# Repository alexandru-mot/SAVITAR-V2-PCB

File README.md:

# Savitar V2

Line-follower robot mainboard, designed in KiCad 10.

## Board overview

- **MCU**: ATSAMD51J19A (main), ESP32-C3-MINI-1 (wireless/telemetry)
- **USB**: USB-C input with USBLC6-2 ESD protection and an FSUSB42 USB mux
- **Power**: MT2492 buck converter + TLV75733 LDO
- **Motor drive**: dual DRV8874 H-bridges with INA240 current sensing (see the "Motor" netclass in the project settings)
- **Line sensing**: QRE1113GR IR-reflectance array, muxed through 74HC4051/74HC238, driven via a TBD62083 array, connected over FFC to the main board

## Schematic hierarchy

- `SAVITAR_V2.kicad_sch` — root sheet
  - `MCU.kicad_sch` — MCU, power, USB, motor drive
  - `SENSOR_ARRAY.kicad_sch` — IR sensor array board

## Libraries

Project-local only, referenced via `${KIPRJMOD}`:
- `symbols/SAVITAR` — consolidated project symbol library
- `footprints/SAVITAR.pretty` — consolidated project footprint library
- `models/` — 3D step models

## BOM

`BOM/SAVITAR_V2_BOM.csv` is generated directly from the schematic (reference designators, values, footprints) and is the source of truth for what's actually on the board. Regenerate it after schematic changes with:

```
kicad-cli sch export bom --group-by "Value,Footprint" --output "BOM/SAVITAR_V2_BOM.csv" "SAVITAR_V2.kicad_sch"
```

An `LCSC#` + `Notes` column has been added by hand, carried over from an earlier LCSC cart export (`BOM/archive/`). Rows with a note are either genuinely ambiguous (two different LCSC SKUs existed for the same value), not yet sourced, or flagged for a spec mismatch — check the `Notes` column before ordering. **LCSC stock/pricing changes constantly — treat this column as something to refresh right before placing an order, not something to keep current during layout.**

## Backups

`SAVITAR_V2-backups/` is local-only (gitignored) — timestamped project backups, not versioned since git already provides history.

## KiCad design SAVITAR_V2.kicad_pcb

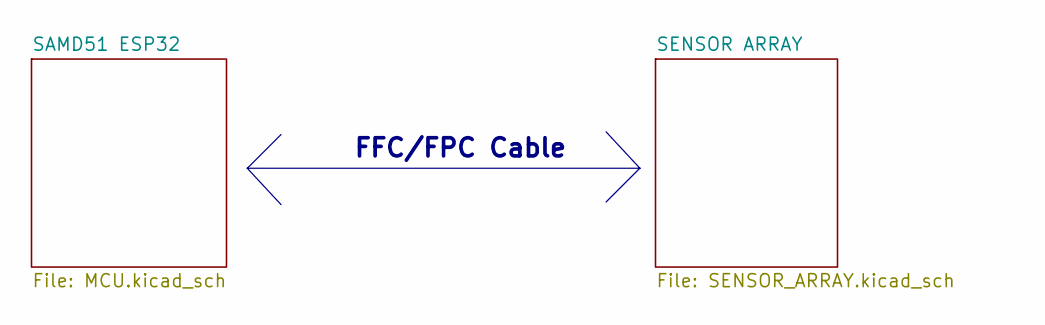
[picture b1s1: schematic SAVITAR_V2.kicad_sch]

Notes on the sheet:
FFC/FPC Cable

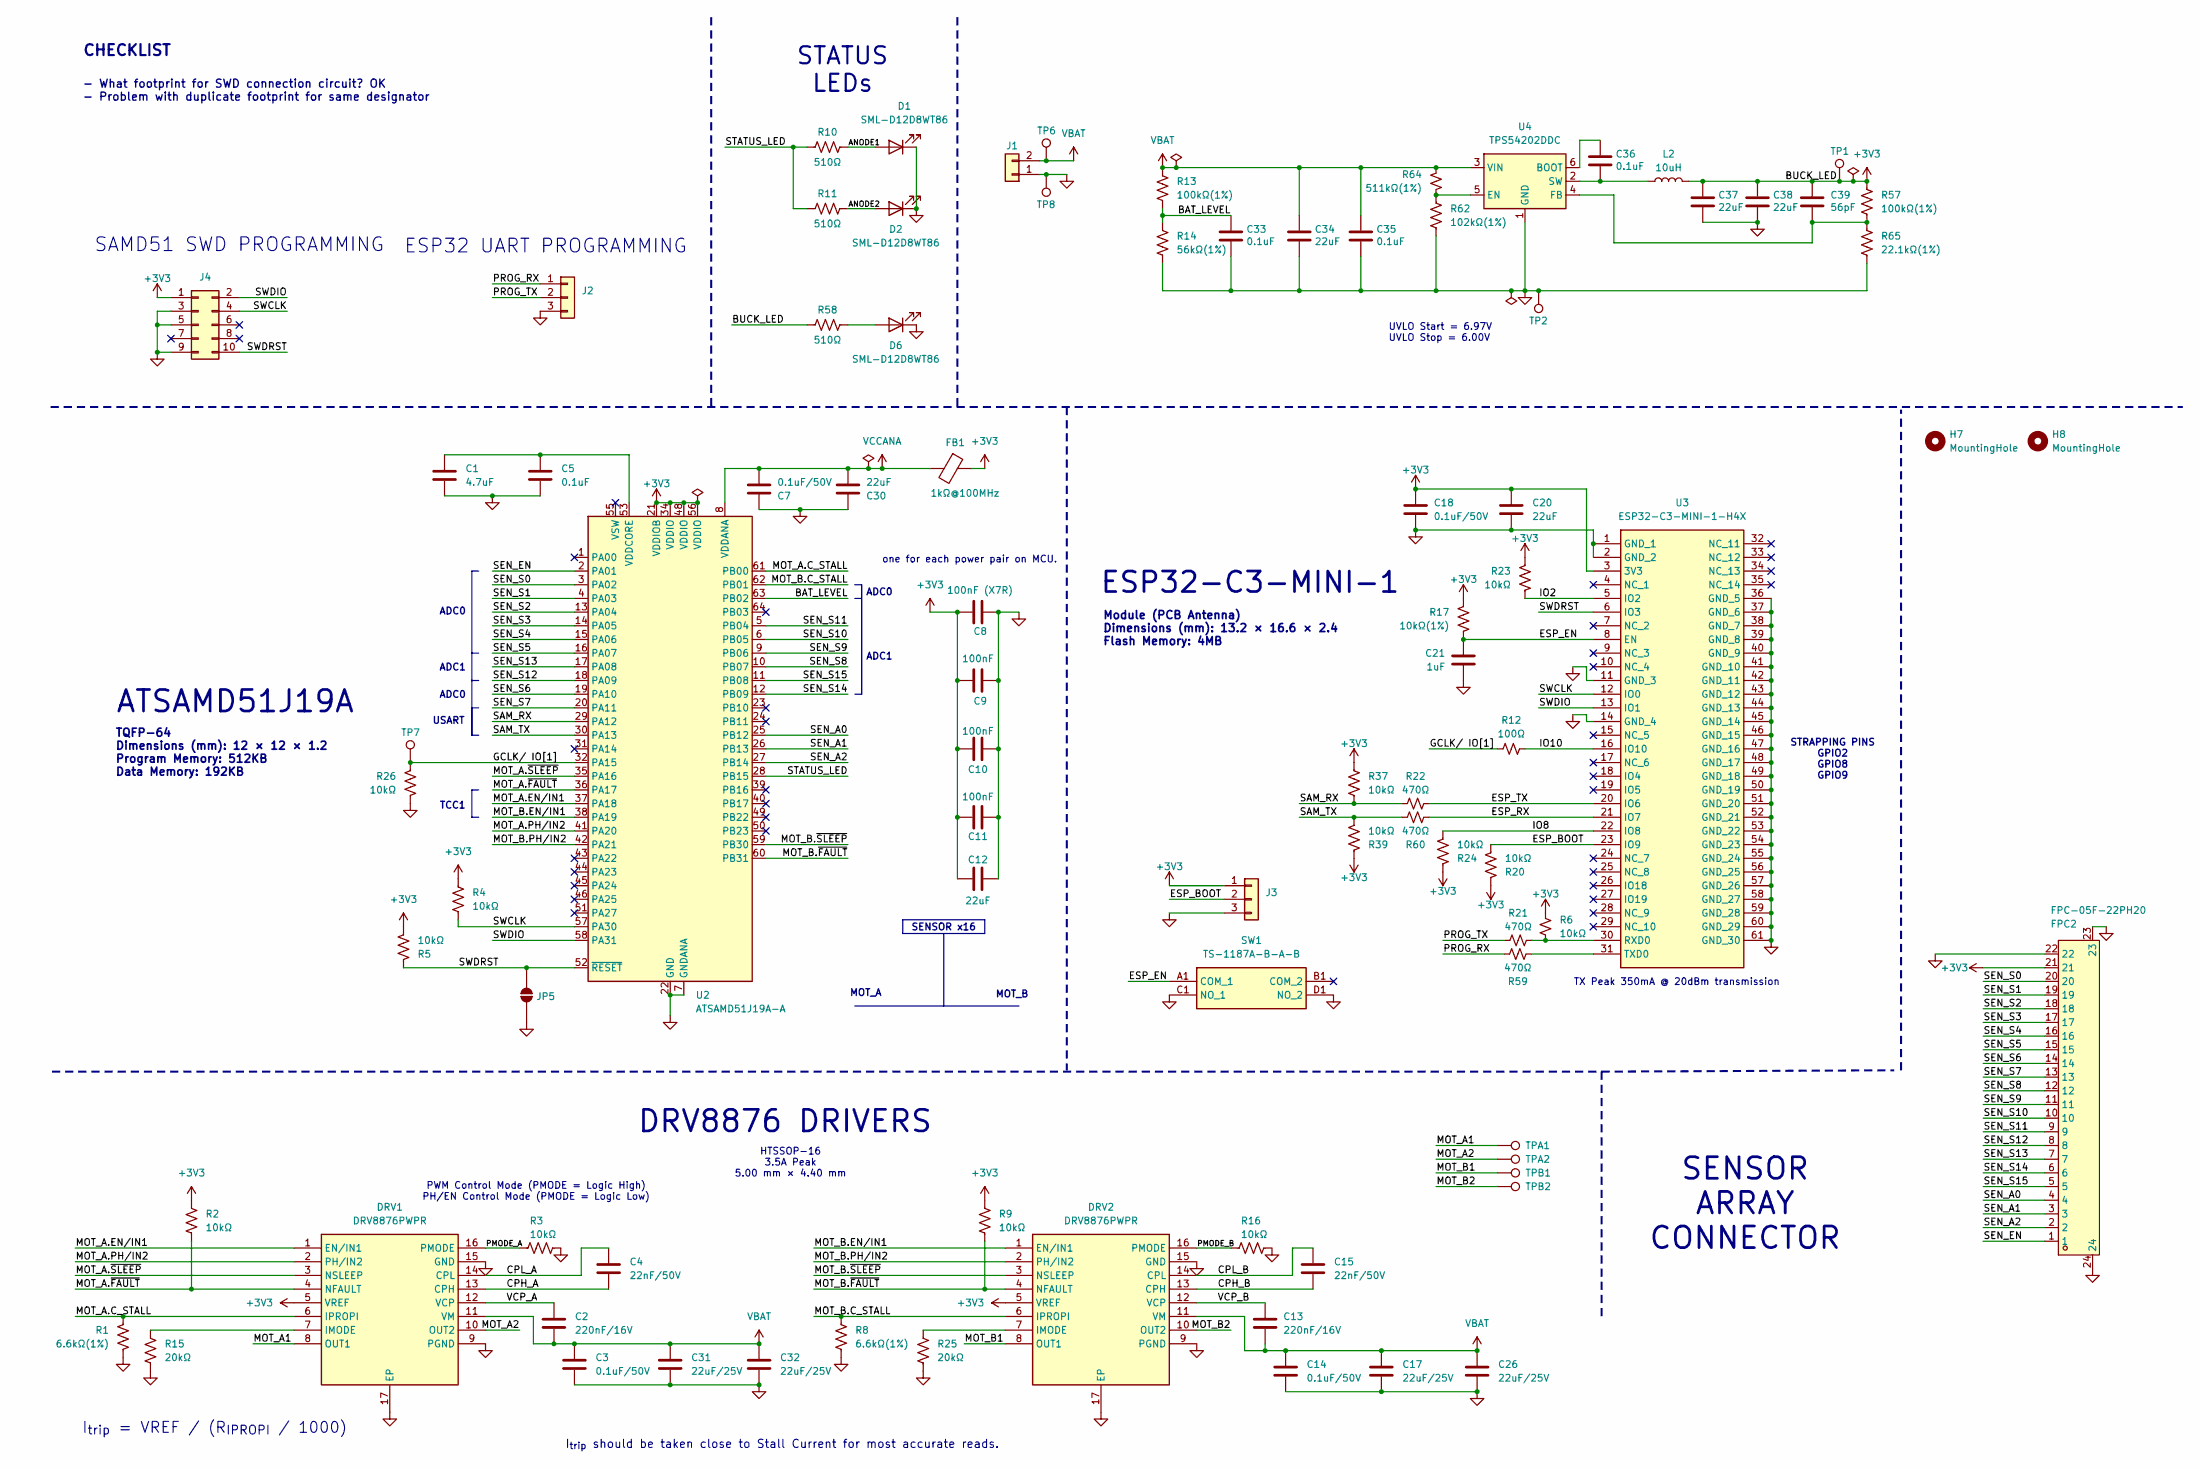
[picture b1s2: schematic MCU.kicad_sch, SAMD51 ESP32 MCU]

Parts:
C1: 4.7uF; C_0603_1608Metric_Pad1.08x0.95mm_HandSolder
C2, C13: 220nF/16V; C_0402_1005Metric_Pad0.74x0.62mm_HandSolder
C3, C7, C14, C18: 0.1uF/50V; C_0402_1005Metric_Pad0.74x0.62mm_HandSolder
C4, C15: 22nF/50V; C_0402_1005Metric_Pad0.74x0.62mm_HandSolder
C5, C33, C35, C36: 0.1uF; C_0402_1005Metric_Pad0.74x0.62mm_HandSolder
C8: 100nF (X7R); C_0402_1005Metric_Pad0.74x0.62mm_HandSolder
C9, C10, C11: 100nF; C_0402_1005Metric_Pad0.74x0.62mm_HandSolder
C12, C20, C30, C34, C37, C38: 22uF; C_0805_2012Metric_Pad1.18x1.45mm_HandSolder
C17, C26, C31, C32: 22uF/25V; C_0805_2012Metric_Pad1.18x1.45mm_HandSolder
C21: 1uF; C_0402_1005Metric_Pad0.74x0.62mm_HandSolder
C39: 56pF; C_0402_1005Metric_Pad0.74x0.62mm_HandSolder
D1, D2, D6: SML-D12D8WT86; LED_0603_1608Metric_Pad1.05x0.95mm_HandSolder
DRV1, DRV2: DRV8876PWPR; SOP65P640X120-17N; Manufacturer_Part_Number DRV8874PWPR; Mouser Part Number 595-DRV8874PWPR
FB1: 1kΩ@100MHz; L_0805_2012Metric
FPC2: FPC-05F-22PH20; FPC-SMD_22P-P0.50_FPC-05F-22PH20; MPN FPC-05F-22PH20; LCSC Part C2856804
H7, H8: MountingHole; MountingHole_3.2mm_M3
J1: Conn_01x02; JST_PH_S2B-PH-K_1x02_P2.00mm_Horizontal
J2, J3: Conn_01x03; PinHeader_1x03_P2.54mm_Vertical
J4: Conn_02x05_Odd_Even; PinHeader_2x05_P1.27mm_Vertical_SMD
JP5: SolderJumper_2_Open; SolderJumper-2_P1.3mm_Open_RoundedPad1.0x1.5mm
L2: 10uH; L_APV_ANR3015; LCSC Part # C19634061
R1, R8: 6.6kΩ(1%); R_0402_1005Metric_Pad0.72x0.64mm_HandSolder
R2, R3, R4, R5, R6, R9, R16, R20, R23, R24, R26, R37, R39: 10kΩ; R_0402_1005Metric_Pad0.72x0.64mm_HandSolder
R10, R11, R58: 510Ω; R_0402_1005Metric_Pad0.72x0.64mm_HandSolder
R12: 100Ω; R_0402_1005Metric_Pad0.72x0.64mm_HandSolder
R13, R57: 100kΩ(1%); R_0402_1005Metric_Pad0.72x0.64mm_HandSolder
R14: 56kΩ(1%); R_0402_1005Metric_Pad0.72x0.64mm_HandSolder
R15, R25: 20kΩ; R_0402_1005Metric_Pad0.72x0.64mm_HandSolder
R17: 10kΩ(1%); R_0402_1005Metric_Pad0.72x0.64mm_HandSolder
R21, R22, R59, R60: 470Ω; R_0402_1005Metric_Pad0.72x0.64mm_HandSolder
R62: 102kΩ(1%); R_0402_1005Metric_Pad0.72x0.64mm_HandSolder
R64: 511kΩ(1%); R_0402_1005Metric_Pad0.72x0.64mm_HandSolder
R65: 22.1kΩ(1%); R_0402_1005Metric_Pad0.72x0.64mm_HandSolder
SW1: TS-1187A-B-A-B; TS1187ABAB; Manufacturer_Part_Number TS-1187A-B-A-B
TP1, TP2, TP6, TP7, TP8: TestPoint; TestPoint_Pad_D1.5mm
TPA1, TPA2: TestPoint; TestPoint_THTPad_2.0x2.0mm_Drill1.0mm
TPB1, TPB2: TestPoint; TestPoint_THTPad_2.0x2.0mm_Drill1.0mm
U2: ATSAMD51J19A-A; TQFP-64_10x10mm_P0.5mm
U3: ESP32-C3-MINI-1-H4X; ESP32C3MINI1H4X; Manufacturer_Part_Number ESP32-C3-MINI-1-H4X; Mouser Part Number 356-ESP32C3MINI1H4X
U4: TPS54202DDC; SOT-23-6

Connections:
+3V3: C8.2, C9.2, C10.2, C11.2, C12.1, C18.2, C20.1, C37.1, C38.1, C39.1, DRV1.5 (VREF), DRV2.5 (VREF), FB1.1, FPC2.21, J3.1, J4.1, L2.2, R2.1, R4.1, R5.2, R6.1, R9.1, R17.1, R20.1, R23.1, R24.1, R37.1, R39.1, R57.2, R58.1, TP1.1 (1_1), U2.21 (VDDIOB), U2.34 (VDDIO), U2.48 (VDDIO), U2.56 (VDDIO), U3.3 (3V3); also elsewhere on the board
/SAMD51 ESP32/ANODE1: D1.2 (A), R10.2
/SAMD51 ESP32/ANODE2: D2.2 (A), R11.2
/SAMD51 ESP32/BAT_LEVEL: C33.1, R13.1, R14.2, U2.63 (PB02)
/SAMD51 ESP32/CPH_A: C4.1, DRV1.13 (CPH)
/SAMD51 ESP32/CPH_B: C15.1, DRV2.13 (CPH)
/SAMD51 ESP32/CPL_A: C4.2, DRV1.14 (CPL)
/SAMD51 ESP32/CPL_B: C15.2, DRV2.14 (CPL)
/SAMD51 ESP32/ESP_BOOT: J3.2, R20.2, U3.23 (IO9)
/SAMD51 ESP32/ESP_EN: C21.2, R17.2, SW1.A1 (COM_1), U3.8 (EN)
/SAMD51 ESP32/ESP_RX: R60.1, U3.21 (IO7)
/SAMD51 ESP32/ESP_TX: R22.2, U3.20 (IO6)
/SAMD51 ESP32/GCLK/ IO[1]: R12.1, R26.1, TP7.1 (1_1), U2.32 (PA15); also elsewhere on the board
/SAMD51 ESP32/IO2: R23.2, U3.5 (IO2)
/SAMD51 ESP32/IO8: R24.2, U3.22 (IO8)
/SAMD51 ESP32/IO10: R12.2, U3.16 (IO10); also elsewhere on the board
/SAMD51 ESP32/MOT_A1: DRV1.8 (OUT1), TPA1.1 (1_1)
/SAMD51 ESP32/MOT_A2: DRV1.10 (OUT2), TPA2.1 (1_1)
/SAMD51 ESP32/MOT_A.C_STALL: DRV1.6 (IPROPI), R1.1, U2.61 (PB00)
/SAMD51 ESP32/MOT_A.EN/IN1: DRV1.1 (EN/IN1), U2.37 (PA18)
/SAMD51 ESP32/MOT_A.PH/IN2: DRV1.2 (PH/IN2), U2.41 (PA20)
/SAMD51 ESP32/MOT_A.~FAULT: DRV1.4 (NFAULT), R2.2, U2.36 (PA17)
/SAMD51 ESP32/MOT_A.~SLEEP: DRV1.3 (NSLEEP), U2.35 (PA16)
/SAMD51 ESP32/MOT_B1: DRV2.8 (OUT1), TPB1.1 (1_1)
/SAMD51 ESP32/MOT_B2: DRV2.10 (OUT2), TPB2.1 (1_1)
/SAMD51 ESP32/MOT_B.C_STALL: DRV2.6 (IPROPI), R8.1, U2.62 (PB01)
/SAMD51 ESP32/MOT_B.EN/IN1: DRV2.1 (EN/IN1), U2.38 (PA19)
/SAMD51 ESP32/MOT_B.PH/IN2: DRV2.2 (PH/IN2), U2.42 (PA21)
/SAMD51 ESP32/MOT_B.~FAULT: DRV2.4 (NFAULT), R9.2, U2.60 (PB31)
/SAMD51 ESP32/MOT_B.~SLEEP: DRV2.3 (NSLEEP), U2.59 (PB30)
/SAMD51 ESP32/PMODE_A: DRV1.16 (PMODE), R3.2
/SAMD51 ESP32/PMODE_B: DRV2.16 (PMODE), R16.2
/SAMD51 ESP32/PROG_RX: J2.1, R59.2
/SAMD51 ESP32/PROG_TX: J2.2, R21.1
/SAMD51 ESP32/SAM_RX: R22.1, R37.2, U2.29 (PA12)
/SAMD51 ESP32/SAM_TX: R39.2, R60.2, U2.30 (PA13)
/SAMD51 ESP32/SEN_A0: FPC2.4, U2.25 (PB12)
/SAMD51 ESP32/SEN_A1: FPC2.3, U2.26 (PB13)
/SAMD51 ESP32/SEN_A2: FPC2.2, U2.27 (PB14)
/SAMD51 ESP32/SEN_EN: FPC2.1, U2.2 (PA01)
/SAMD51 ESP32/SEN_S0: FPC2.20, U2.3 (PA02)
/SAMD51 ESP32/SEN_S1: FPC2.19, U2.4 (PA03)
/SAMD51 ESP32/SEN_S2: FPC2.18, U2.13 (PA04)
/SAMD51 ESP32/SEN_S3: FPC2.17, U2.14 (PA05)
/SAMD51 ESP32/SEN_S4: FPC2.16, U2.15 (PA06)
/SAMD51 ESP32/SEN_S5: FPC2.15, U2.16 (PA07)
/SAMD51 ESP32/SEN_S6: FPC2.14, U2.19 (PA10)
/SAMD51 ESP32/SEN_S7: FPC2.13, U2.20 (PA11)
/SAMD51 ESP32/SEN_S8: FPC2.12, U2.10 (PB07)
/SAMD51 ESP32/SEN_S9: FPC2.11, U2.9 (PB06)
/SAMD51 ESP32/SEN_S10: FPC2.10, U2.6 (PB05)
/SAMD51 ESP32/SEN_S11: FPC2.9, U2.5 (PB04)
/SAMD51 ESP32/SEN_S12: FPC2.8, U2.18 (PA09)
/SAMD51 ESP32/SEN_S13: FPC2.7, U2.17 (PA08)
/SAMD51 ESP32/SEN_S14: FPC2.6, U2.12 (PB09)
/SAMD51 ESP32/SEN_S15: FPC2.5, U2.11 (PB08)
/SAMD51 ESP32/STATUS_LED: R10.1, R11.1, U2.28 (PB15)
/SAMD51 ESP32/SWCLK: J4.4, R4.2, U2.57 (PA30), U3.12 (IO0)
/SAMD51 ESP32/SWDIO: J4.2, U2.58 (PA31), U3.13 (IO1)
/SAMD51 ESP32/SWDRST: J4.10, JP5.1 (A), R5.1, U2.52 (~RESET), U3.6 (IO3)
/SAMD51 ESP32/VCP_A: C2.2, DRV1.12 (VCP)
/SAMD51 ESP32/VCP_B: C13.2, DRV2.12 (VCP)
GND: C1.1, C3.1, C5.1, C7.2, C8.1, C9.1, C10.1, C11.1, C12.2, C14.1, C17.1, C18.1, C20.2, C21.1, C26.1, C30.2, C31.1, C32.1, C33.2, C34.2, C35.2, C37.2, C38.2, D1.1 (K), D2.1 (K), D6.1 (K), DRV1.9 (PGND), DRV1.15 (GND), DRV1.17 (EP), DRV2.9 (PGND), DRV2.15 (GND), DRV2.17 (EP), FPC2.22, FPC2.23, FPC2.24, J1.1, J2.3, J3.3, J4.3, J4.5, J4.9, JP5.2 (B), R1.2, R3.1, R8.2, R14.1, R15.2, R16.1, R25.2, R26.2, R62.1, R65.1, SW1.C1 (NO_1), SW1.D1 (NO_2), TP2.1 (1_1), TP8.1 (1_1), U2.7 (GNDANA), U2.22 (GND), U2.33 (GND), U2.47 (GND), U2.54 (GND), U3.1 (GND_1), U3.2 (GND_2), U3.11 (GND_3), U3.14 (GND_4), U3.36 (GND_5), U3.37 (GND_6), U3.38 (GND_7), U3.39 (GND_8), U3.40 (GND_9), U3.41 (GND_10), U3.42 (GND_11), U3.43 (GND_12), U3.44 (GND_13), U3.45 (GND_14), U3.46 (GND_15), U3.47 (GND_16), U3.48 (GND_17), U3.49 (GND_18), U3.50 (GND_19), U3.51 (GND_20), U3.52 (GND_21), U3.53 (GND_22), U3.54 (GND_23), U3.55 (GND_24), U3.56 (GND_25), U3.57 (GND_26), U3.58 (GND_27), U3.59 (GND_28), U3.60 (GND_29), U3.61 (GND_30), U4.1 (GND); also elsewhere on the board
unnamed: D6.2 (A), R58.2
unnamed: DRV1.7 (IMODE), R15.1
unnamed: DRV2.7 (IMODE), R25.1
unnamed 106: C1.2, C5.2, U2.53 (VDDCORE); also elsewhere on the board
unnamed: R6.2, R21.2, U3.30 (RXD0)
unnamed: R59.1, U3.31 (TXD0)
unnamed: C36.1, U4.6 (BOOT)
unnamed: R62.2, R64.2, U4.5 (EN)
unnamed: C39.2, R57.1, R65.2, U4.4 (FB)
unnamed: C36.2, L2.1, U4.2 (SW)
VBAT: C2.1, C3.2, C13.1, C14.2, C17.2, C26.2, C31.2, C32.2, C34.1, C35.1, DRV1.11 (VM), DRV2.11 (VM), J1.2, R13.2, R64.1, TP6.1 (1_1), U4.3 (VIN)
VCCANA: C7.1, C30.1, FB1.2, U2.8 (VDDANA); also elsewhere on the board

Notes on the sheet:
TCC1
HTSSOP-16 3.5A Peak 5.00 mm × 4.40 mm
ESP32-C3-MINI-1
ADC0
SENSOR ARRAY CONNECTOR
SENSOR x16
UVLO Start = 6.97V UVLO Stop = 6.00V
MOT_B
TX Peak 350mA @ 20dBm transmission
DRV8876 DRIVERS
STRAPPING PINS GPIO2 GPIO8 GPIO9
Module (PCB Antenna) Dimensions (mm): 13.2 × 16.6 × 2.4 Flash Memory: 4MB
PWM Control Mode (PMODE = Logic High) PH/EN Control Mode (PMODE = Logic Low)
TQFP-64 Dimensions (mm): 12 × 12 × 1.2 Program Memory: 512KB Data Memory: 192KB
- What footprint for SWD connection circuit? OK - Problem with duplicate footprint for same designator
STATUS LEDs
SAMD51 SWD PROGRAMMING
ADC1
one for each power pair on MCU.
ATSAMD51J19A
MOT_A
I_{trip} = VREF / (R_{IPROPI} / 1000)
I_{trip} should be taken close to Stall Current for most accurate reads.
CHECKLIST
ESP32 UART PROGRAMMING
USART

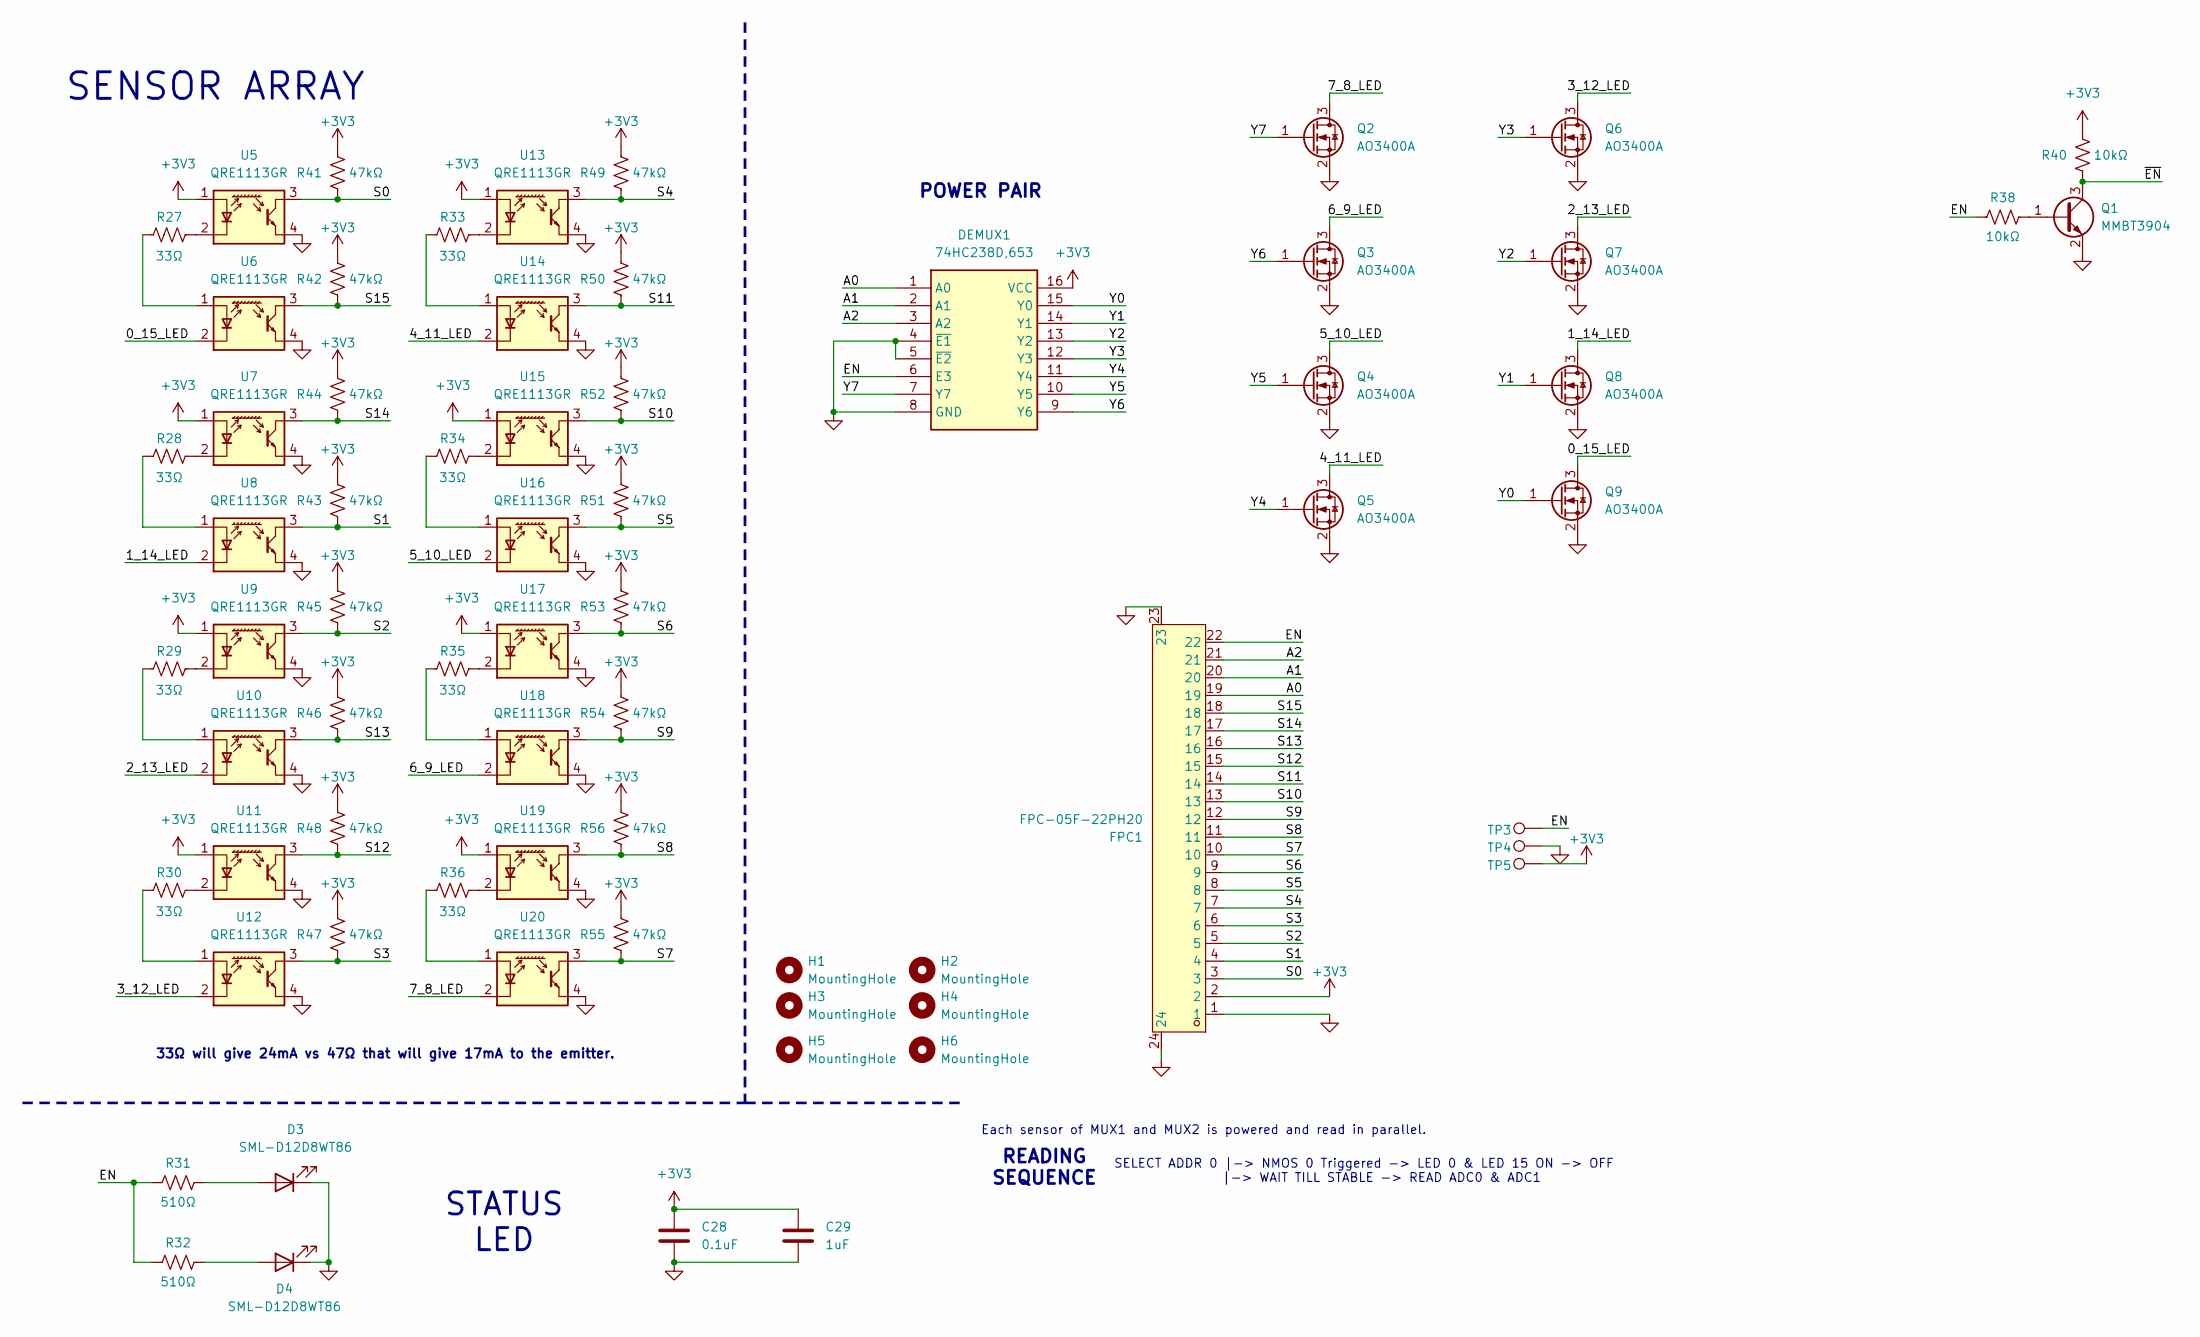
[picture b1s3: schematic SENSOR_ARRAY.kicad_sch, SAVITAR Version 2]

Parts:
C28: 0.1uF; C_0402_1005Metric_Pad0.74x0.62mm_HandSolder
C29: 1uF; C_0402_1005Metric_Pad0.74x0.62mm_HandSolder
D3, D4: SML-D12D8WT86; LED_0603_1608Metric_Pad1.05x0.95mm_HandSolder
DEMUX1: 74HC238D,653; 74HC238D653; Manufacturer_Part_Number 74HC238D,653; Mouser Part Number 771-74HC238D-T
FPC1: FPC-05F-22PH20; FPC-SMD_22P-P0.50_FPC-05F-22PH20; MPN FPC-05F-22PH20; LCSC Part C2856804
H1, H2, H3, H4: MountingHole; MountingHole_2.2mm_M2_DIN965_Pad
H5, H6: MountingHole; MountingHole_3.2mm_M3
Q1: MMBT3904; SOT-23
Q2, Q3, Q4, Q5, Q6, Q7, Q8, Q9: AO3400A; SOT-23
R27, R28, R29, R30, R33, R34, R35, R36: 33Ω; R_0402_1005Metric_Pad0.72x0.64mm_HandSolder
R31, R32: 510Ω; R_0402_1005Metric_Pad0.72x0.64mm_HandSolder
R38, R40: 10kΩ; R_0402_1005Metric
R41, R42, R43, R44, R45, R46, R47, R48, R49, R50, R51, R52, R53, R54, R55, R56: 47kΩ; R_0402_1005Metric_Pad0.72x0.64mm_HandSolder
TP3, TP4, TP5: TestPoint; TestPoint_Pad_D1.5mm
U5, U6, U7, U8, U9, U10, U11, U12, U13, U14, U15, U16, U17, U18, U19, U20: QRE1113GR; OnSemi_CASE100CY

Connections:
+3V3: C28.1, C29.1, DEMUX1.16 (VCC), FPC1.2, R40.2, R41.2, R42.2, R43.2, R44.2, R45.2, R46.2, R47.2, R48.2, R49.2, R50.2, R51.2, R52.2, R53.2, R54.2, R55.2, R56.2, TP5.1 (1_1), U5.1 (A), U7.1 (A), U9.1 (A), U11.1 (A), U13.1 (A), U15.1 (A), U17.1 (A), U19.1 (A); also elsewhere on the board
/SENSOR ARRAY/0_15_LED: Q9.3 (D), U6.2 (K)
/SENSOR ARRAY/1_14_LED: Q8.3 (D), U8.2 (K)
/SENSOR ARRAY/2_13_LED: Q7.3 (D), U10.2 (K)
/SENSOR ARRAY/3_12_LED: Q6.3 (D), U12.2 (K)
/SENSOR ARRAY/4_11_LED: Q5.3 (D), U14.2 (K)
/SENSOR ARRAY/5_10_LED: Q4.3 (D), U16.2 (K)
/SENSOR ARRAY/6_9_LED: Q3.3 (D), U18.2 (K)
/SENSOR ARRAY/7_8_LED: Q2.3 (D), U20.2 (K)
/SENSOR ARRAY/A0: DEMUX1.1 (A0), FPC1.19
/SENSOR ARRAY/A1: DEMUX1.2 (A1), FPC1.20
/SENSOR ARRAY/A2: DEMUX1.3 (A2), FPC1.21
/SENSOR ARRAY/EN: DEMUX1.6 (E3), FPC1.22, R31.1, R32.1, R38.1, TP3.1 (1_1)
/SENSOR ARRAY/S0: FPC1.3, R41.1, U5.3
/SENSOR ARRAY/S1: FPC1.4, R43.1, U8.3
/SENSOR ARRAY/S2: FPC1.5, R45.1, U9.3
/SENSOR ARRAY/S3: FPC1.6, R47.1, U12.3
/SENSOR ARRAY/S4: FPC1.7, R49.1, U13.3
/SENSOR ARRAY/S5: FPC1.8, R51.1, U16.3
/SENSOR ARRAY/S6: FPC1.9, R53.1, U17.3
/SENSOR ARRAY/S7: FPC1.10, R55.1, U20.3
/SENSOR ARRAY/S8: FPC1.11, R56.1, U19.3
/SENSOR ARRAY/S9: FPC1.12, R54.1, U18.3
/SENSOR ARRAY/S10: FPC1.13, R52.1, U15.3
/SENSOR ARRAY/S11: FPC1.14, R50.1, U14.3
/SENSOR ARRAY/S12: FPC1.15, R48.1, U11.3
/SENSOR ARRAY/S13: FPC1.16, R46.1, U10.3
/SENSOR ARRAY/S14: FPC1.17, R44.1, U7.3
/SENSOR ARRAY/S15: FPC1.18, R42.1, U6.3
/SENSOR ARRAY/Y0: DEMUX1.15 (Y0), Q9.1 (G)
/SENSOR ARRAY/Y1: DEMUX1.14 (Y1), Q8.1 (G)
/SENSOR ARRAY/Y2: DEMUX1.13 (Y2), Q7.1 (G)
/SENSOR ARRAY/Y3: DEMUX1.12 (Y3), Q6.1 (G)
/SENSOR ARRAY/Y4: DEMUX1.11 (Y4), Q5.1 (G)
/SENSOR ARRAY/Y5: DEMUX1.10 (Y5), Q4.1 (G)
/SENSOR ARRAY/Y6: DEMUX1.9 (Y6), Q3.1 (G)
/SENSOR ARRAY/Y7: DEMUX1.7 (Y7), Q2.1 (G)
GND: C28.2, C29.2, D3.1 (K), D4.1 (K), DEMUX1.4 (~E1), DEMUX1.5 (~E2), DEMUX1.8 (GND), FPC1.1, FPC1.23, FPC1.24, Q1.2 (E), Q2.2 (S), Q3.2 (S), Q4.2 (S), Q5.2 (S), Q6.2 (S), Q7.2 (S), Q8.2 (S), Q9.2 (S), TP4.1 (1_1), U5.4, U6.4, U7.4, U8.4, U9.4, U10.4, U11.4, U12.4, U13.4, U14.4, U15.4, U16.4, U17.4, U18.4, U19.4, U20.4; also elsewhere on the board
unnamed: D3.2 (A), R31.2
unnamed: D4.2 (A), R32.2
unnamed: Q1.1 (B), R38.2
unnamed: Q1.3 (C), R40.1
unnamed: R27.2, U5.2 (K)
unnamed: R27.1, U6.1 (A)
unnamed: R28.2, U7.2 (K)
unnamed: R28.1, U8.1 (A)
unnamed: R29.2, U9.2 (K)
unnamed: R29.1, U10.1 (A)
unnamed: R30.2, U11.2 (K)
unnamed: R30.1, U12.1 (A)
unnamed: R33.2, U13.2 (K)
unnamed: R33.1, U14.1 (A)
unnamed: R34.2, U15.2 (K)
unnamed: R34.1, U16.1 (A)
unnamed: R35.2, U17.2 (K)
unnamed: R35.1, U18.1 (A)
unnamed: R36.2, U19.2 (K)
unnamed: R36.1, U20.1 (A)

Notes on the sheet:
SELECT ADDR 0 |-> NMOS 0 Triggered -> LED 0 & LED 15 ON -> OFF |-> WAIT TILL STABLE -> READ ADC0 & ADC1
Each sensor of MUX1 and MUX2 is powered and read in parallel.
STATUS LED
POWER PAIR
READING SEQUENCE
SENSOR ARRAY
33Ω will give 24mA vs 47Ω that will give 17mA to the emitter.

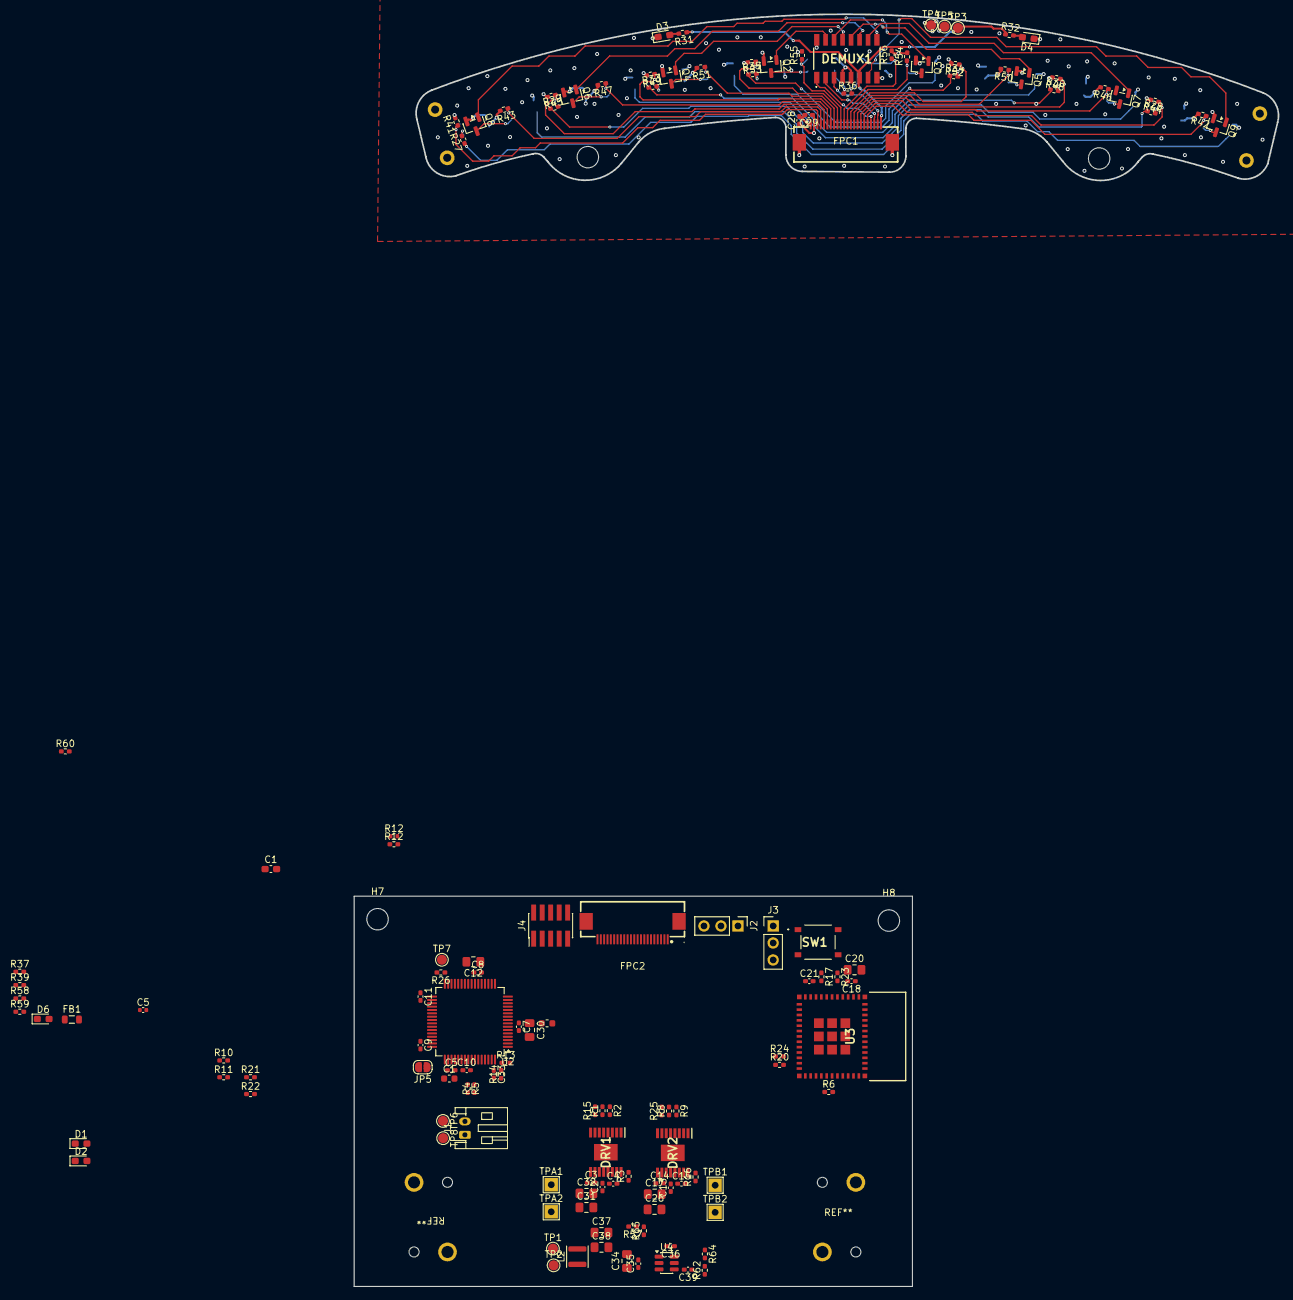
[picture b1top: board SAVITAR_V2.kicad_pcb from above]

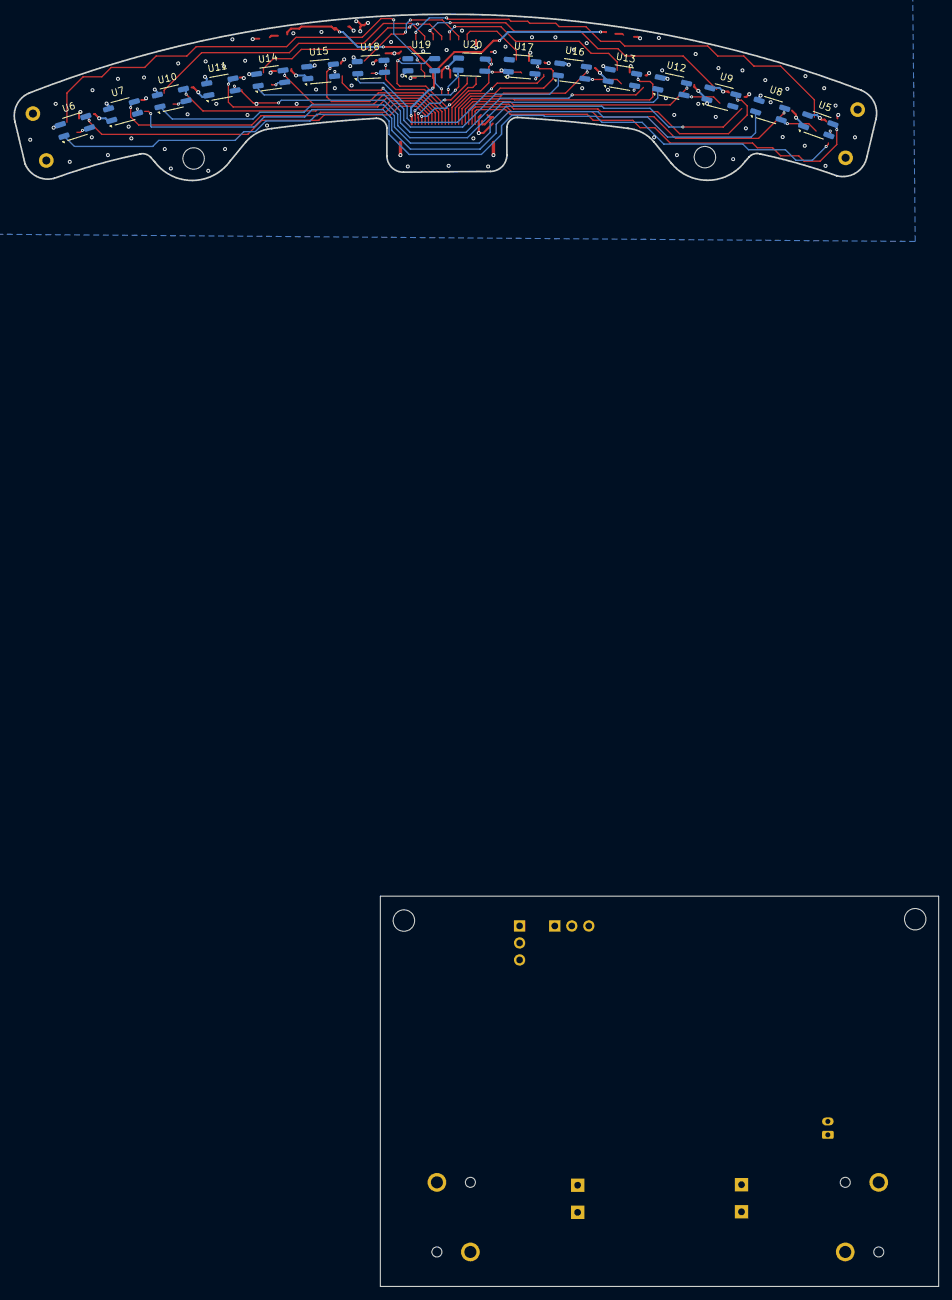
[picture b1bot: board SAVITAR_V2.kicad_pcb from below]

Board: 4 copper layers, 138.1 x 190.0 mm, 158 parts (16 on the bottom side), 129 nets.

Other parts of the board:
C1#2: 4.7uF (X7R); C_0603_1608Metric
C5#2: 1uF (X7R); C_0402_1005Metric
FB1#2: 380mΩ 500mA; L_0603_1608Metric
R12#2: 100Ω; R_0402_1005Metric

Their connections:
/SAMD51 ESP32/GCLK/ IO[1]: R12#2.1; also elsewhere on the board
/SAMD51 ESP32/IO10: R12#2.2; also elsewhere on the board
GND: C1#2.1, C5#2.2; also elsewhere on the board
unnamed 106: C1#2.2, C5#2.1; also elsewhere on the board
VCCANA: FB1#2.2; also elsewhere on the board

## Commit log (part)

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2026-05-10 Initial commit.
2026-05-10 Added gitignore
2026-05-12 Added Decoder 3x8 (74HC238D) and 8 NMOS array (TBD62083AFNG) for driving the LEDs in pairs of 2 (±40 mA) only when they are read.
2026-05-14 Changed schematic structure. Separated sensor array from PD processing and motor control. Sensor schematic is finished. Moving to MCU wiring. All project symbols and footprints are under SAVITAR name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
2026-05-14 Started designing main schematic. Added DRV8833 circuit with 2 motors attached.
2026-05-14 Added power regulation using buck DC-DC switching regulator MT2492 and an LDO LD1117S33CTR for clearing ripple.
2026-05-17 Changed motor driver from DRV8874 to a simpler, small-footprint DRV8837 using the IN1/IN2 interface.
2026-05-19 Added ESP32-C3-MINI-1 circuit for the PD control over AP STA. Added comments and read sequence explanation. The schematic is finished, please add tag.
2026-05-20 Added dedicated Current Sensing IC INA240. Changed Buck output from 3.8V (edge of Teensy's LDO supply voltage) to 5V.
2026-05-21 Added decoupling for sensor board. Changed the relatively old CD4051BM with over 400 ohm to 74HC4051. Added for the first time hierarchical label to connect the FFC pins across schematics.
2026-05-23 Added 3D models to third party footprints. Final Teensy version, switching to SAMD51 custom setup. Please add tag.
2026-05-26 Add main board: power tree, USB-C, ESP32-C3, dual DRV8874 motor drive
    Power:
    - Add 100nF per-pin decoupling + 22uF bulk on SAMD51 supplies
    - Add 120R@100MHz/2A ferrite bead on VDDANA for ADC supply isolation
    - Change buck output 5V -> 3.8V; inductor 22uH -> 6.8uH; FB R7 13.7k -> 18.7k
    - Add 22pF feedforward cap across buck FB top resistor
    - Keep TLV75733 LDO (fed from 3.8V) for 3.3V rail; dissipation now ~0.15W
2026-05-28 Made passives smaller from 0603 to 0402 because I will solder them with hot air gun anyway. Started positioning SAMD51 bypass caps.
